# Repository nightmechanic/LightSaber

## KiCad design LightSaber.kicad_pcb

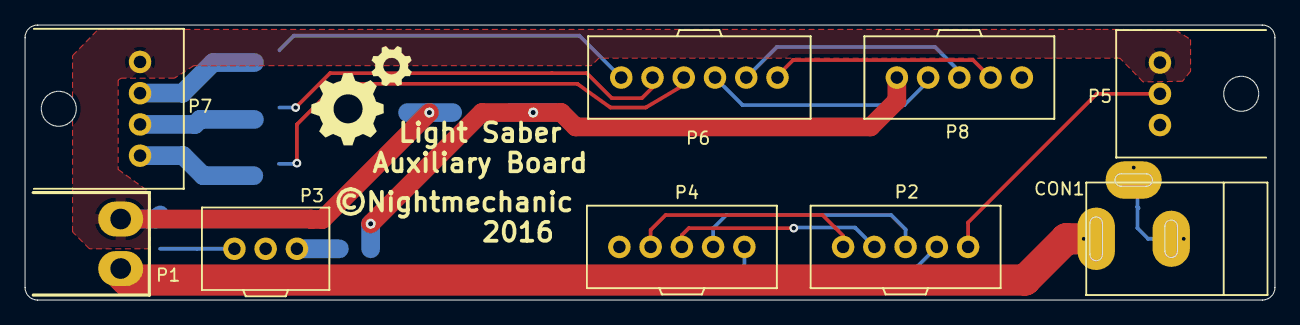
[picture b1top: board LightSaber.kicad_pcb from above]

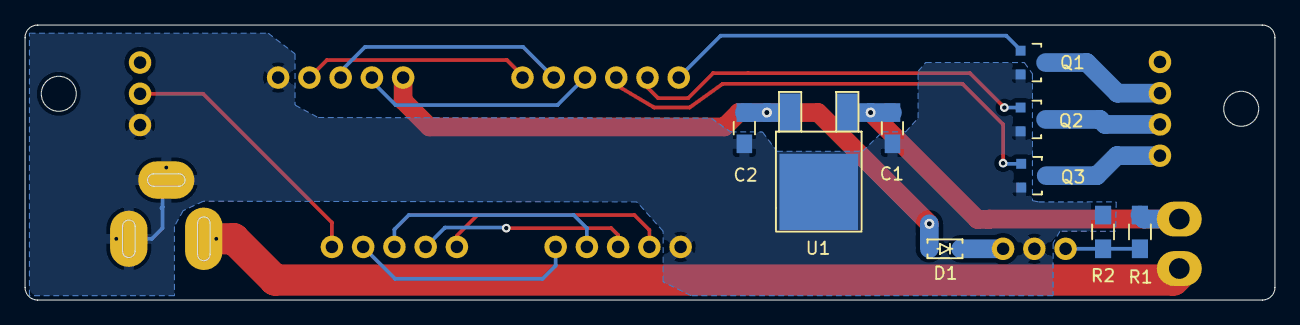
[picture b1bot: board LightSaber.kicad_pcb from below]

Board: 2 copper layers, 100.0 x 22.0 mm, 19 parts (9 on the bottom side), 20 nets.

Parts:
C1, C2: 0.33uF; C_0805_HandSoldering
CON1: BARREL_JACK; CDI_BARREL_JACK
D1: BAS3010B; SOD-323
P1: JST_B2PS_VH; B2PS-VH
P2, P4, P8: JST_B05B-XASK-1; JST_B05B_XASK_1
P3: JST_B03B-XASK-1; JST_B03B_XASK_1
P5: JST_S03B-XASK-1; JST_S03B_XASK_1
P6: JST_B06B-XASK-1; JST_B06B_XASK_1
P7: JST_S04B-XASK-1; JST_S04B_XASK_1
Q1, Q2, Q3: Si2312CDS; SOT-23
R1: 47k; R_0805_HandSoldering
R2: 10k; R_0805_HandSoldering
U1: MC78M05CDT; TO-252-2Lead-D-PAK
VAL: REF; Gears_F.SilkS_10mm

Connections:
+5V: C2.1, D1.2, P8.1, U1.3
+12V: C1.1, P1.2, P5.3, P7.1, R1.1, U1.1
/MCU_AUDIO: P2.1, P5.2
/MCU_B_LED: P6.3, Q3.1
/MCU_G_LED: P6.2, Q2.1
/MCU_INT: P6.6, P8.4
/MCU_R_LED: P6.1, Q1.1
/MCU_SCK: P6.4, P8.2
/MCU_SDA: P6.5, P8.3
/MCU_SW1: P2.2, P4.1
/MCU_SW2: P2.3, P4.2
/MCU_SW3: P2.4, P4.3
/MCU_SW4: P2.5, P4.4
/V_Batt: CON1.1, P1.1
GND: C1.2, C2.2, CON1.2, CON1.3, P3.2, P4.5, P5.1, P8.5, Q1.2, Q2.2, Q3.2, R2.2, U1.2
unnamed: D1.1, P3.1
unnamed: P3.3, R1.2, R2.1
unnamed: P7.2, Q1.3
unnamed: P7.3, Q2.3
unnamed: P7.4, Q3.3

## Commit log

2016-03-30 :space_invader: Added .gitattributes & .gitignore files
2016-03-30 First published version

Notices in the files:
LightSaber.kicad_pcb:
©Nightmechanic
